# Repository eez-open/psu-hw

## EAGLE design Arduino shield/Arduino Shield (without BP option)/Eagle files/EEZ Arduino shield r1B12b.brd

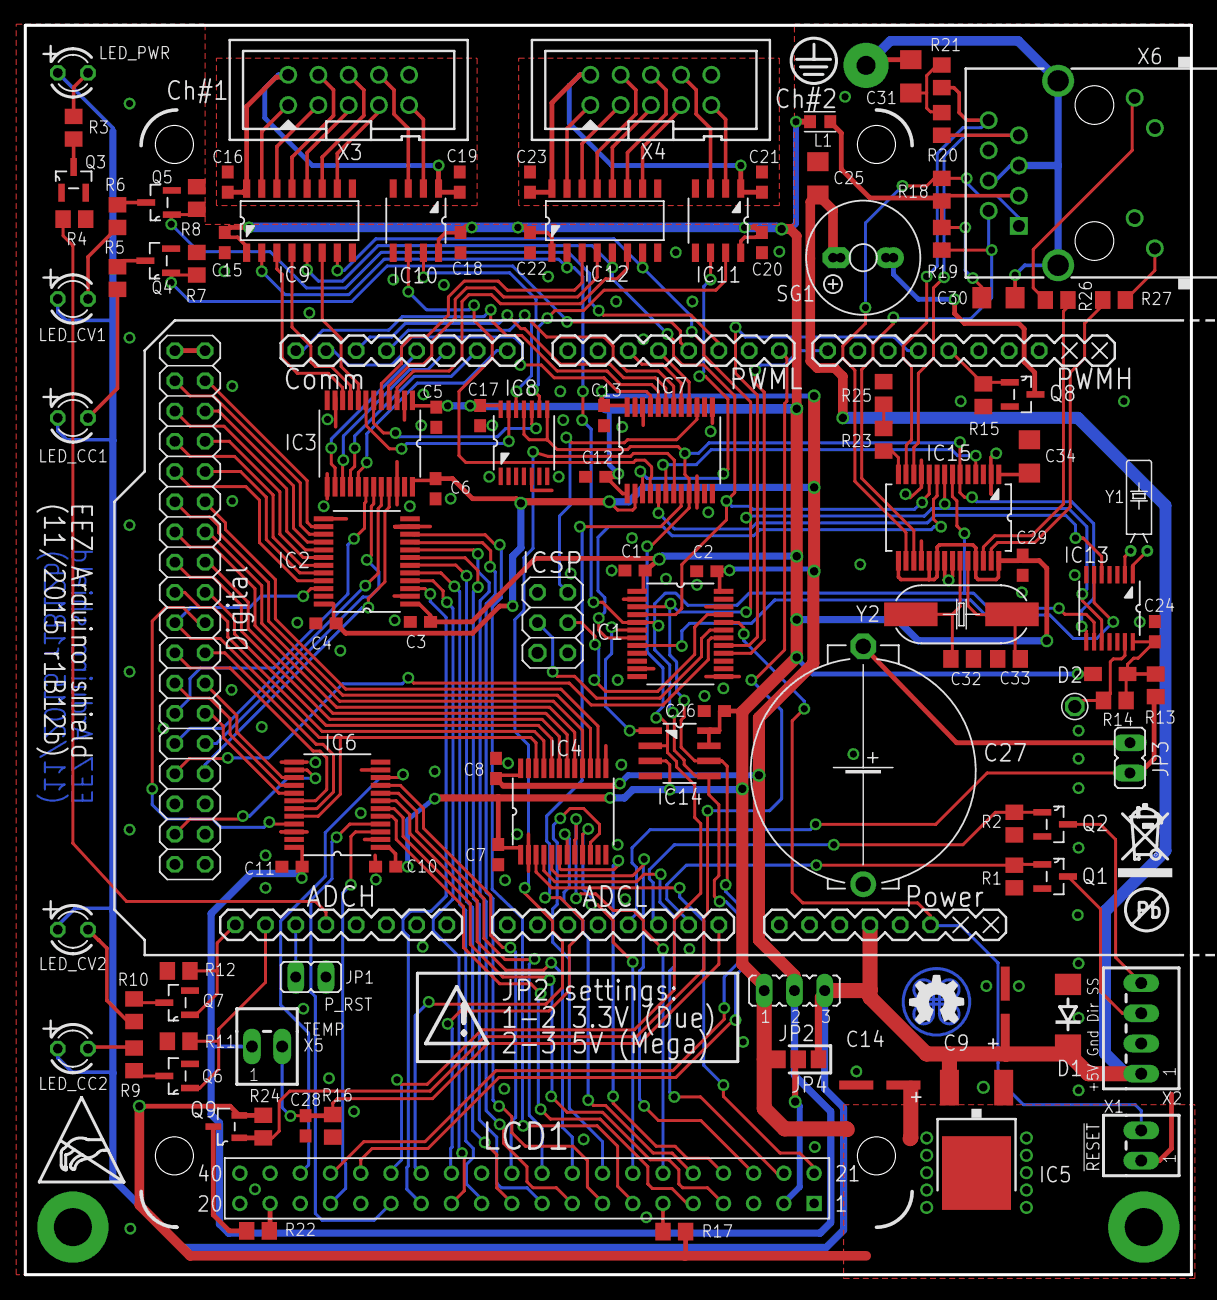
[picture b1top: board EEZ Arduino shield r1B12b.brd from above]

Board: 3 copper layers, 98.0 x 105.0 mm, 114 parts (1 on the bottom side), 167 nets.

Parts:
C1, C2, C3, C4, C5, C6, C7, C8, C10, C11, C12, C13, C15, C16, C17, C18, C19, C20, C21, C22, C23, C24, C26, C28, C29: 100n; C0603
C9: 47u; PANASONIC_C
C14: 10u; PANASONIC_C
C25, C34: 10u; C1206
C27: EECS5R5H105; SG-R20MM
C30, C31: 10n; C1206
C32, C33: 18p; C0805
D1: SMBJ5.0A-TR; DO214AA
D2: BAS316; SOD323-W
EEZ_SIGNATURE: SIGNATURESMALL; SIGNATURE_5MM
IC1, IC2, IC3, IC4, IC6, IC7: SN74LVCC3245ADBRSSOP; SOP65P780X200-24N
IC5: LD1117ADT33TR; DPACK
IC8: SN74LV125APW; SOP65P640X120-14N
IC9, IC12: Si8660EC-B-IS1; SOIC-16
IC10, IC11: SI8620EC-B-IS; SOIC127P600X173-8N
IC13: PCA21125; SOP65P640X120-14N
IC14: AT25256B; SOIC127P600X175-8N
IC15: ENC28J60-I/SS; SOP65P780X200-28N
JP1, JP3: 826926-2; JP1
JP2: 826926-3; JUMPER_3-PIN
JP4: 0R-JUMPA; A0R-JMP
L1: 60R@100MHz; BEAD0603
LCD1: TFT_320QVT; LCD_TFT_320QVT_MIRROR
LED_CC1, LED_CC2: L-934ID; LED3MM
LED_CV1, LED_CV2: L-934YD; LED3MM
LED_PWR: L-934MBC; LED3MM
MCU: ARDUINO+ICSP_MIRROR
Q1, Q2, Q3, Q4, Q5, Q6, Q7, Q8: 2N7002; SOT103P240X110-3N
Q9: IRLML2246TRPBF; SOT95P237X112-3N
R1, R2, R4, R7, R8, R11, R12, R15, R24: 100K; R0805
R3, R5, R6, R9, R10: 240R; R0805
R13: 560R; R0805
R14, R17: 10K; R0805
R16: 4K7; R0805
R18, R19, R20, R21: 50R 0.1%; R0805
R22: 10R; R0805
R23: 2K2 1%; R0805
R25: 120R 1%; R0805
R26, R27: 200R; R0805
SG1: LD-BZEN-0903; BUZZER
SW1: 1301.9316; TACTM-6XN
TP1: PCB_SHIELD_TAB
U$2: RECYCLE_BIN1/8
U$3: PB_SMALL
U$4: ESD_SYMBOL
X1, X5: 22-23-2021
X2: 22-23-2041
X3, X4: 09185106324; IDC-10PIN
X6: LMJTAB881243M-L; RJ45-TRAFO-LED
Y1: 32,768kHz; R26_XTAL
Y2: 25MHz; HC-49/4H

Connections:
3V3LCDSD_CS: IC6.10, LCD1.38
3V3LCD_CS: IC6.4, LCD1.15
3V3LCD_DB0: IC4.3, LCD1.21
3V3LCD_DB1: IC4.4, LCD1.22
3V3LCD_DB2: IC4.5, LCD1.23
3V3LCD_DB3: IC4.6, LCD1.24
3V3LCD_DB4: IC4.7, LCD1.25
3V3LCD_DB5: IC4.8, LCD1.26
3V3LCD_DB6: IC4.9, LCD1.27
3V3LCD_DB7: IC4.10, LCD1.28
3V3LCD_DB8: IC2.10, LCD1.7
3V3LCD_DB9: IC2.9, LCD1.8
3V3LCD_DB10: IC2.8, LCD1.9
3V3LCD_DB11: IC2.7, LCD1.10
3V3LCD_DB12: IC2.6, LCD1.11
3V3LCD_DB13: IC2.5, LCD1.12
3V3LCD_DB14: IC2.4, LCD1.13
3V3LCD_DB15: IC2.3, LCD1.14
3V3LCD_RD: LCD1.6, R17.1
3V3LCD_RESET: IC6.3, LCD1.17
3V3LCD_RS: IC6.6, LCD1.4
3V3LCD_WR: IC6.5, LCD1.5
3V3MISO: IC7.9, IC8.8, IC8.11, IC13.8, IC14.2, IC15.6, LCD1.35
3V3MOSI: IC1.5, IC9.2, IC12.2, IC13.9, IC14.5, IC15.7, LCD1.37
3V3SCLK: IC1.3, IC9.7, IC12.7, IC13.10, IC14.6, IC15.8, LCD1.36
3V3TOUCH_CS: IC6.8, LCD1.30
3V3TOUCH_DIN: IC6.9, LCD1.31
3V3TOUCH_DO: IC7.8, LCD1.33
3V3TOUCH_IRQ: IC7.7, LCD1.34
3V3TOUCH_SCLK: IC6.7, LCD1.29
!3V3ADC1_SELECT: IC3.8, IC9.6
!3V3ADC2_SELECT: IC3.3, IC12.6
!3V3CONVEND1: IC7.4, IC10.6
!3V3CONVEND2: IC7.3, IC11.6
!3V3DAC1_SELECT: IC3.9, IC9.4
!3V3DAC2_SELECT: IC3.4, IC12.4
!3V3EEPROM_SELECT: IC1.6, IC14.1
!3V3ETH_IRQ: IC7.6, IC15.4
!3V3ETH_SELECT: IC1.7, IC15.9
!3V3IO_EXPANDER1: IC3.10, IC9.3
!3V3IO_EXPANDER2: IC3.5, IC12.3
!3V3ISOLATOR1_EN: IC3.7, IC8.13
!3V3ISOLATOR2_EN: IC3.6, IC8.10
!3V3RESET: IC1.4, IC9.5, IC12.5, IC15.10
!3V3RTC_IRQ: IC7.5, IC13.5
!3V3RTC_SELECT: IC1.8, IC13.6
!ADC1_SELECT: IC3.16, MCU.15
!ADC2_SELECT: IC3.21, MCU.48
!CH1_ADC: IC9.11, X3.6
!CH1_DAC: IC9.13, X3.4
!CH1_EXPANDER: IC9.14, X3.3
!CH1_INT: IC10.3, X3.8
!CH1_RESET: IC9.12, X3.5
!CH2_ADC: IC12.11, X4.6
!CH2_DAC: IC12.13, X4.4
!CH2_EXPANDER: IC12.14, X4.3
!CH2_INT: IC11.3, X4.8
!CH2_RESET: IC12.12, X4.5
!CONVEND1: IC7.20, MCU.21
!CONVEND2: IC7.21, MCU.20
!DAC1_SELECT: IC3.15, MCU.16
!DAC2_SELECT: IC3.20, MCU.47
!EEPROM_SELECT: IC1.18, MCU.49
!ETH_IRQ: IC7.18, MCU.18
!ETH_SELECT: IC1.17, MCU.11
!IO_EXPANDER1: IC3.14, MCU.17
!IO_EXPANDER2: IC3.19, MCU.46
!ISOLATOR1_EN: IC3.17, MCU.14
!ISOLATOR2_EN: IC3.18, MCU.45
!PWD_RST: JP1.1, MCU.A13
!RESET: IC1.20, MCU.RESET, SW1.3, SW1.4, X1.2
!RTC_IRQ: IC7.19, MCU.19
!RTC_SELECT: IC1.16, MCU.8
+3V3: C1.1, C3.1, C5.1, C7.1, C10.1, C12.1, C14.1, C15.1, C17.2, C18.1, C20.1, C22.1, C26.1, C29.1, D2.A, IC1.1, IC2.1, IC3.1, IC4.1, IC5.4, IC6.1, IC7.1, IC8.14, IC9.1, IC10.8, IC11.8, IC12.1, IC14.3, IC14.7, IC14.8, IC15.15, IC15.19, IC15.20, IC15.25, IC15.28, JP2.1, JP4.3, L1.P$2, Q9.2, R17.2, R24.2
+5V: C9.1, C25.2, D1.C, IC5.3, JP2.3, JP4.1, LED_CC1.A, LED_CC2.A, LED_CV1.A, LED_CV2.A, LED_PWR.A, MCU.5V, SG1.+, SG1.+B, X2.1
BUZZER: MCU.12, Q8.1, R15.2
CH1_5VDC: C16.1, C19.1, IC9.16, IC10.1, X3.2
CH1_GND: C16.2, C19.2, IC9.9, IC10.4, X3.10
CH1_MISO: IC10.2, X3.9
CH1_MOSI: IC9.15, X3.1
CH1_SCLK: IC9.10, X3.7
CH2_5VDC: C21.1, C23.1, IC11.1, IC12.16, X4.2
CH2_GND: C21.2, C23.2, IC11.4, IC12.9, X4.10
CH2_MISO: IC11.2, X4.9
CH2_MOSI: IC12.15, X4.1
CH2_SCLK: IC12.10, X4.7
EARTH: C30.2, C31.2, X6.4, X6.5, X6.SH1, X6.SH2
ETH_IN+: IC15.13, R21.1, X6.8
ETH_IN-: IC15.12, R20.2, X6.7
ETH_LEDA: IC15.26, R26.1
ETH_LEDB: IC15.27, R27.1
ETH_OUT+: IC15.17, R19.1, X6.2
ETH_OUT-: IC15.16, R18.2, X6.1
GND: C1.2, C2.1, C3.2, C4.1, C5.2, C6.1, C7.2, C8.1, C9.2, C10.2, C11.1, C12.2, C13.1, C14.2, C15.2, C17.1, C18.2, C20.2, C22.2, C24.1, C25.1, C26.2, C27.2, C28.1, C29.2, C32.2, C33.2, C34.1, D1.A, IC1.2, IC1.11, IC1.12, IC1.13, IC1.14, IC1.15, IC1.22, IC2.2, IC2.11, IC2.12, IC2.13, IC3.2, IC3.11, IC3.12, IC3.13, IC3.22, IC4.2, IC4.11, IC4.12, IC4.13, IC5.1, IC6.2, IC6.11, IC6.12, IC6.13, IC6.22, IC7.10, IC7.11, IC7.12, IC7.13, IC7.22, IC8.1, IC8.2, IC8.4, IC8.5, IC8.7, IC9.8, IC10.5, IC11.5, IC12.8, IC13.7, IC14.4, IC15.2, IC15.11, IC15.18, IC15.21, IC15.22, JP1.2, LCD1.1, MCU.GND, MCU.GND1, MCU.GND2, MCU.GND3, MCU.GND4, MCU.ICSP_GND, Q1.2, Q2.2, Q3.2, Q4.2, Q5.2, Q6.2, Q7.2, Q8.2, R1.2, R2.2, R4.2, R7.2, R8.2, R11.2, R12.2, R15.1, R16.2, R25.2, SW1.1, SW1.2, SW1.5, X1.1, X2.2, X6.10, X6.11
LCDSD_CS: IC6.14, MCU.53
LCD_BRIGHTNESS: MCU.7, Q9.1, R24.1
LCD_CS: IC2.22, IC4.22, IC6.20, MCU.39
LCD_DB0: IC4.21, MCU.37
LCD_DB1: IC4.20, MCU.36
LCD_DB2: IC4.19, MCU.35
LCD_DB3: IC4.18, MCU.34
LCD_DB4: IC4.17, MCU.33
LCD_DB5: IC4.16, MCU.32
LCD_DB6: IC4.15, MCU.31
LCD_DB7: IC4.14, MCU.30
LCD_DB8: IC2.14, MCU.22
LCD_DB9: IC2.15, MCU.23
LCD_DB10: IC2.16, MCU.24
LCD_DB11: IC2.17, MCU.25
LCD_DB12: IC2.18, MCU.26
LCD_DB13: IC2.19, MCU.27
LCD_DB14: IC2.20, MCU.28
LCD_DB15: IC2.21, MCU.29
LCD_RESET: IC6.21, MCU.38
LCD_RS: IC6.18, MCU.41
LCD_WR: IC6.19, MCU.40
LED_A: LCD1.19, R22.2
LED_CC1: MCU.4, Q4.1, R7.1
LED_CC2: MCU.A14, Q6.1, R11.1
LED_CV1: MCU.5, Q5.1, R8.1
LED_CV2: MCU.A15, Q7.1, R12.1
LED_PWR: MCU.A12, R4.1
MISO: IC7.15, MCU.ICSP_MISO
MOSI: IC1.19, MCU.ICSP_MOSI
unnamed: Q3.3, R3.2
unnamed: LED_PWR.K, R3.1
unnamed: JP4.2, LCD1.2
unnamed: LED_CV1.K, R6.2
unnamed: Q6.3, R9.2
unnamed: Q9.3, R22.1
unnamed: LED_CV2.K, R10.2
unnamed: LED_CC2.K, R9.1
unnamed: MCU.5V(1), MCU.5V(2)
unnamed: Q4.3, R5.2
unnamed: Q7.3, R10.1
unnamed: IC13.1, Y1.2
unnamed: IC13.2, Y1.1
unnamed: Q5.3, R6.1
unnamed: LED_CC1.K, R5.1
unnamed: R23.2, R25.1
unnamed: Q8.3, SG1.-, SG1.-B
unnamed: IC13.13, R14.2, TP1.1
unnamed: C27.1, JP3.2
unnamed: C32.1, IC15.23, Y2.2
unnamed: C33.1, IC15.24, Y2.1
unnamed: C34.2, IC15.1
unnamed: IC15.14, R23.1
unnamed: C24.2, D2.C, IC13.14, R13.2, R14.1
unnamed: R26.2, X6.12
unnamed: R27.2, X6.9
unnamed: C31.1, R20.1, R21.2
unnamed: C30.1, L1.P$1, R18.1, R19.2, X6.3
unnamed: IC8.12, IC10.7
unnamed: IC8.9, IC11.7
PWRDIR: MCU.A1, Q1.1, R1.1
PWRSS: MCU.A2, Q2.1, R2.1
PWR_DIRECT: Q1.3, X2.3
PWR_SSTART: Q2.3, X2.4
RTC_BATT: JP3.1, MCU.A3, R13.1
SCLK: IC1.21, MCU.ICSP_SCK
TEMP_ANALOG: C28.2, MCU.A0, R16.1, X5.2
TOUCH_CS: IC6.16, MCU.43
TOUCH_DIN: IC6.15, MCU.42
TOUCH_DOUT: IC7.16, MCU.3
TOUCH_IRQ: IC7.17, MCU.2
TOUCH_SCLK: IC6.17, MCU.44
VCC: C2.2, C4.2, C6.2, C8.2, C11.2, C13.2, IC1.24, IC2.24, IC3.24, IC4.24, IC6.24, IC7.2, IC7.24, JP2.2, X5.1

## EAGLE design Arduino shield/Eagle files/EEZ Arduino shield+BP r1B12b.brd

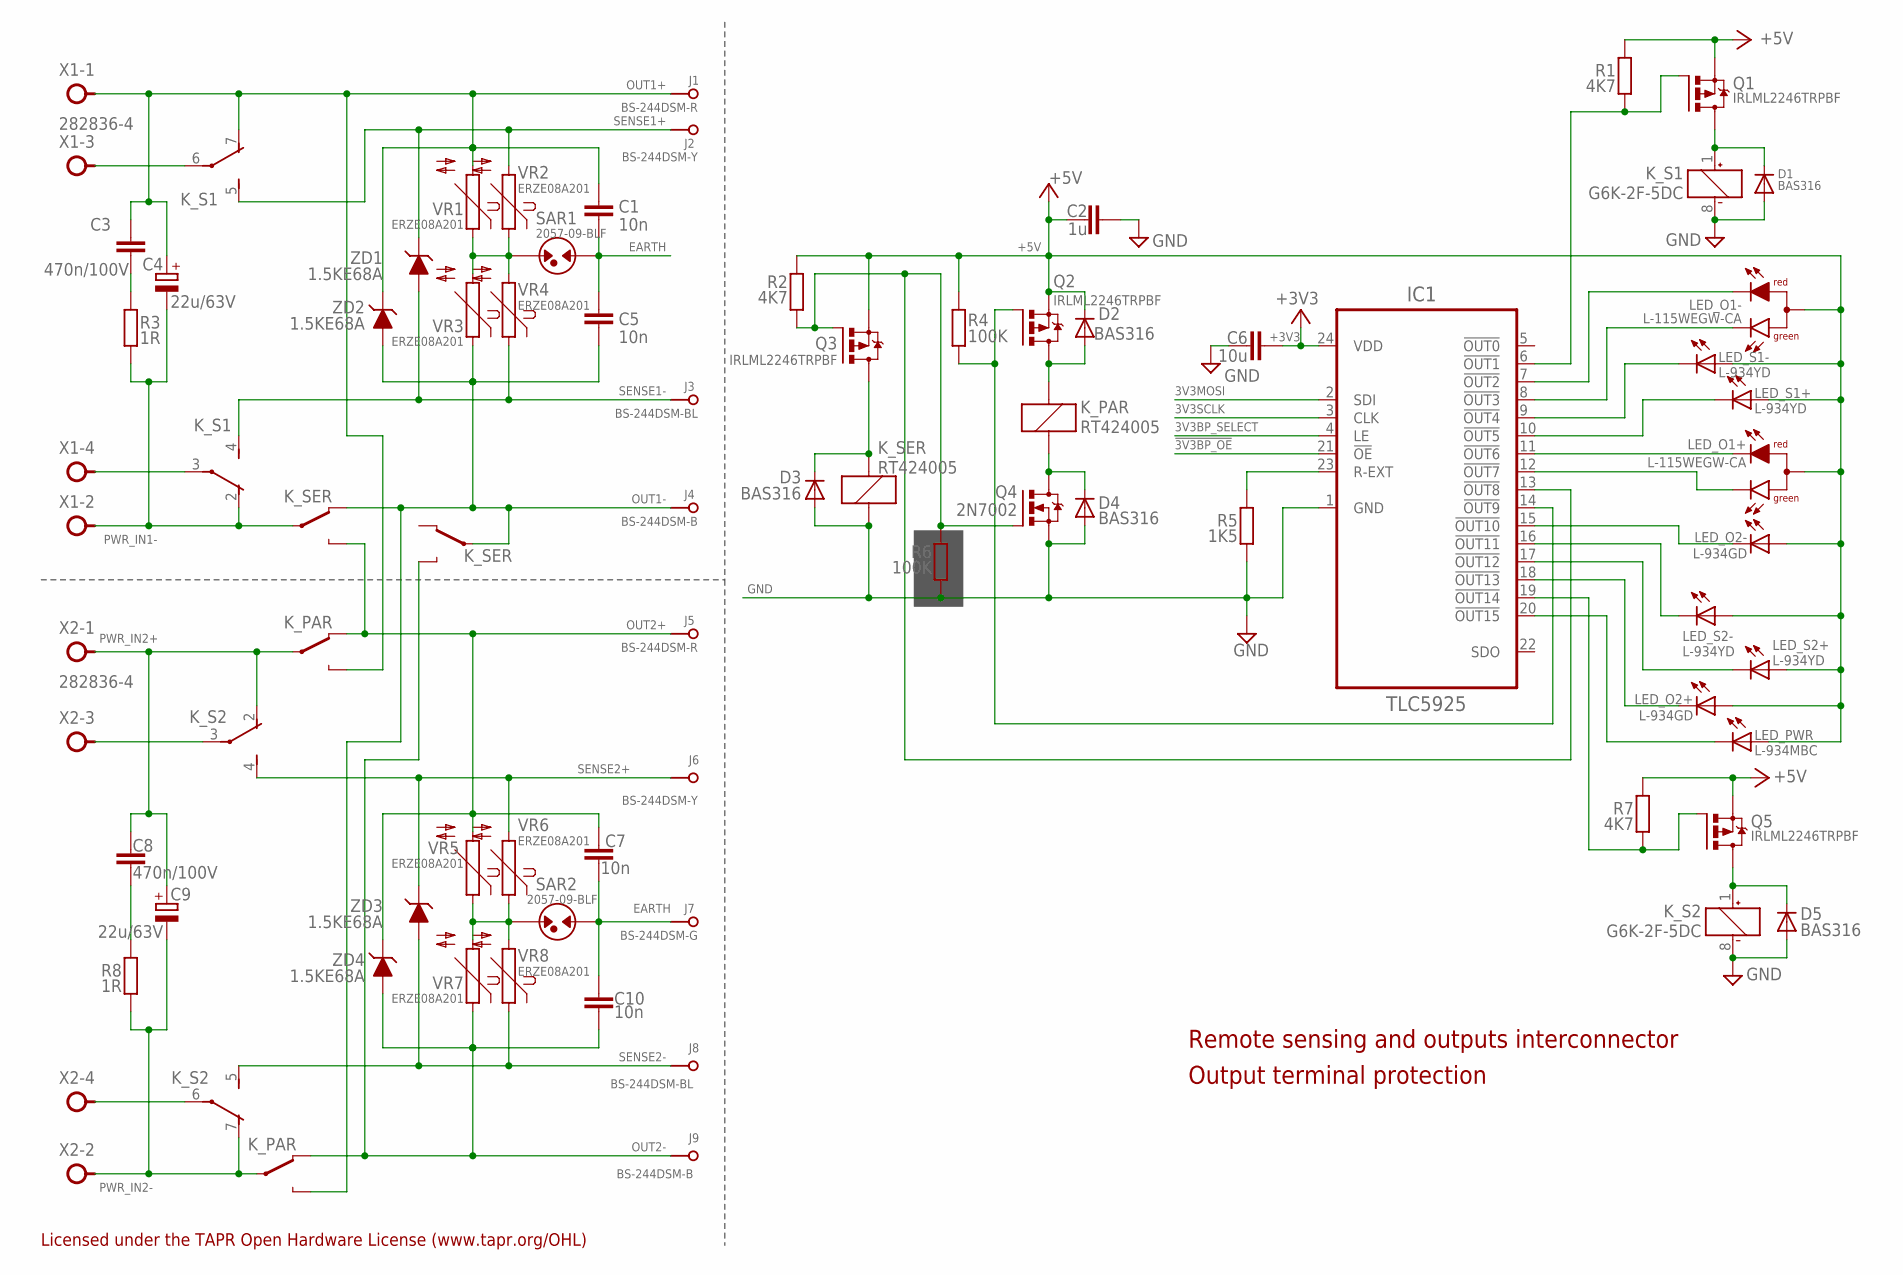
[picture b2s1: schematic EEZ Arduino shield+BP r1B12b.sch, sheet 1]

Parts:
C1, C5, C7, C10: 10n; C1206
C2: 1u; C0805
C3, C8: 470n/100V; C1812
C4, C9: 22u/63V; CAPAE660X610N_COMBO2
C6: 10u; C1206
D1, D2, D3, D4, D5: BAS316; SOD323-W
IC1: TLC5925; SOP63P600X175-24N
J1, J5: BS-244DSM-R; BP_5_12/15WHITE
J2, J6: BS-244DSM-Y; BP_5_12/15BLK
J3, J8: BS-244DSM-BL; BP_5_12/15BLK
J4, J9: BS-244DSM-B; BP_5_12/15WHITE
J7: BS-244DSM-G; BP_5_12/15BLK
K_PAR: RT424005; RT-C/016A5
K_S1, K_S2: G6K-2F-5DC; G6K-2F; MPN G6K-2F DC24
K_SER: RT424005; RT-C/016A5
LED_O1+, LED_O1-: L-115WEGW-CA; DUO_LED3MM
LED_O2+, LED_O2-: L-934GD; LED3MM
LED_PWR: L-934MBC; LED3MM
LED_S1+, LED_S1-, LED_S2+, LED_S2-: L-934YD; LED3MM
Q1, Q2, Q3, Q5: IRLML2246TRPBF; SOT95P237X112-3N
Q4: 2N7002; SOT103P240X110-3N
R1, R2, R7: 4K7; R0805
R3, R8: 1R; R0805
R4, R6: 100K; R0805
R5: 1K5; R0805
SAR1, SAR2: 2057-09-BLF; SAR
VR1, VR2, VR3, VR4, VR5, VR6, VR7, VR8: ERZE08A201; S10K175
X1, X2: 282836-4; TBLOCK5.0_4S
ZD1, ZD2, ZD3, ZD4: 1.5KE68A; DO201

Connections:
3V3BP_SELECT: IC1.4 (LE); also elsewhere on the board
3V3MOSI: IC1.2 (SDI); also elsewhere on the board
3V3SCLK: IC1.3 (CLK); also elsewhere on the board
!3V3BP_OE: IC1.21 (!OE); also elsewhere on the board
!BP_OUT1: IC1.6 (!OUT1), Q1.1 (G), R1.1
!BP_OUT2: IC1.7 (!OUT2), LED_O1-.A (CR)
!BP_OUT3: IC1.8 (!OUT3), LED_O1-.AG (CG)
!BP_OUT4: IC1.9 (!OUT4), LED_S1-.K (C)
!BP_OUT5: IC1.10 (!OUT5), LED_S1+.K (C)
!BP_OUT6: IC1.11 (!OUT6), LED_O1+.A (CR)
!BP_OUT7: IC1.12 (!OUT7), LED_O1+.AG (CG)
!BP_OUT8: IC1.13 (!OUT8), Q3.1 (G), Q4.1 (G), R2.1, R6.2
!BP_OUT9: IC1.14 (!OUT9), Q2.1 (G), R4.1
!BP_OUT10: IC1.15 (!OUT10), LED_O2-.K (C)
!BP_OUT11: IC1.16 (!OUT11), LED_S2-.K (C)
!BP_OUT12: IC1.17 (!OUT12), LED_S2+.K (C)
!BP_OUT13: IC1.18 (!OUT13), LED_O2+.K (C)
!BP_OUT14: IC1.19 (!OUT14), Q5.1 (G), R7.1
!BP_OUT15: IC1.20 (!OUT15), LED_PWR.K (C)
+3V3: C6.1, IC1.24 (VDD); also elsewhere on the board
+5V: C2.1, D2.C, LED_O1+.C (A), LED_O1-.C (A), LED_O2+.A, LED_O2-.A, LED_PWR.A, LED_S1+.A, LED_S1-.A, LED_S2+.A, LED_S2-.A, Q1.2 (S), Q2.2 (S), Q3.2 (S), Q5.2 (S), R1.2, R2.2, R4.2, R7.2; also elsewhere on the board
EARTH: C1.2, C5.1, C7.2, C10.1, J7.P$1, SAR1.P$1, SAR2.P$1; also elsewhere on the board
GND: C2.2, C6.2, D1.A, D3.A, D4.A, D5.A, IC1.1 (GND), K_S1.8 (-), K_S2.8 (-), K_SER.A1 (C2), Q4.2 (S), R5.1, R6.1; also elsewhere on the board
unnamed: K_S2.6, X2.P$4
unnamed: K_S1.6, X1.P$3
unnamed: K_S2.3, X2.P$3
unnamed: D1.C, K_S1.1 (+), Q1.3 (D)
unnamed: D5.C, K_S2.1 (+), Q5.3 (D)
unnamed: C3.2, R3.2
unnamed: C8.2, R8.2
unnamed: K_S1.3, X1.P$4
unnamed: D3.C, K_SER.A2 (C1), Q3.3 (D)
unnamed: D2.A, K_PAR.A1 (C2), Q2.3 (D)
unnamed: IC1.23 (R-EXT), R5.2
unnamed: SAR1.P$2, VR1.1, VR2.1, VR3.2, VR4.2
unnamed: SAR2.P$2, VR5.1, VR6.1, VR7.2, VR8.2
OUT1+: C1.1, C3.1, C4.1 (+), C4.1.1 (+), J1.P$1, K_PAR.14A (O), K_S1.7 (O), VR1.2, X1.P$1, ZD2.C (1)
OUT1-: C5.2, J4.P$1, K_PAR.14B (O), K_SER.11B, K_SER.12A (S), VR3.1, ZD2.A (2)
OUT2+: C7.1, J5.P$1, K_PAR.12A (S), K_SER.14A (O), VR5.2, ZD4.C (1)
OUT2-: C10.2, J9.P$1, K_PAR.12B (S), K_SER.14B (O), VR7.1, ZD4.A (2)
PWR_IN1-: C4.2 (-), C4.2.1 (-), K_S1.2 (O), K_SER.11A, R3.1, X1.P$2
PWR_IN2+: C8.1, C9.1 (+), C9.1.1 (+), K_PAR.11A, K_S2.2 (O), X2.P$1
PWR_IN2-: C9.2 (-), C9.2.1 (-), K_PAR.11B, K_S2.7 (O), R8.1, X2.P$2
SENSE1+: J2.P$1, K_S1.5 (S), VR2.2, ZD1.C (1)
SENSE1-: J3.P$1, K_S1.4 (S), VR4.1, ZD1.A (2)
SENSE2+: J6.P$1, K_S2.4 (S), VR6.2, ZD3.C (1)
SENSE2-: J8.P$1, K_S2.5 (S), VR8.1, ZD3.A (2)
V-2: D4.C, K_PAR.A2 (C1), Q4.3 (D)

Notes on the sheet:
Remote sensing and outputs interconnector
Output terminal protection
Licensed under the TAPR Open Hardware License (www.tapr.org/OHL)

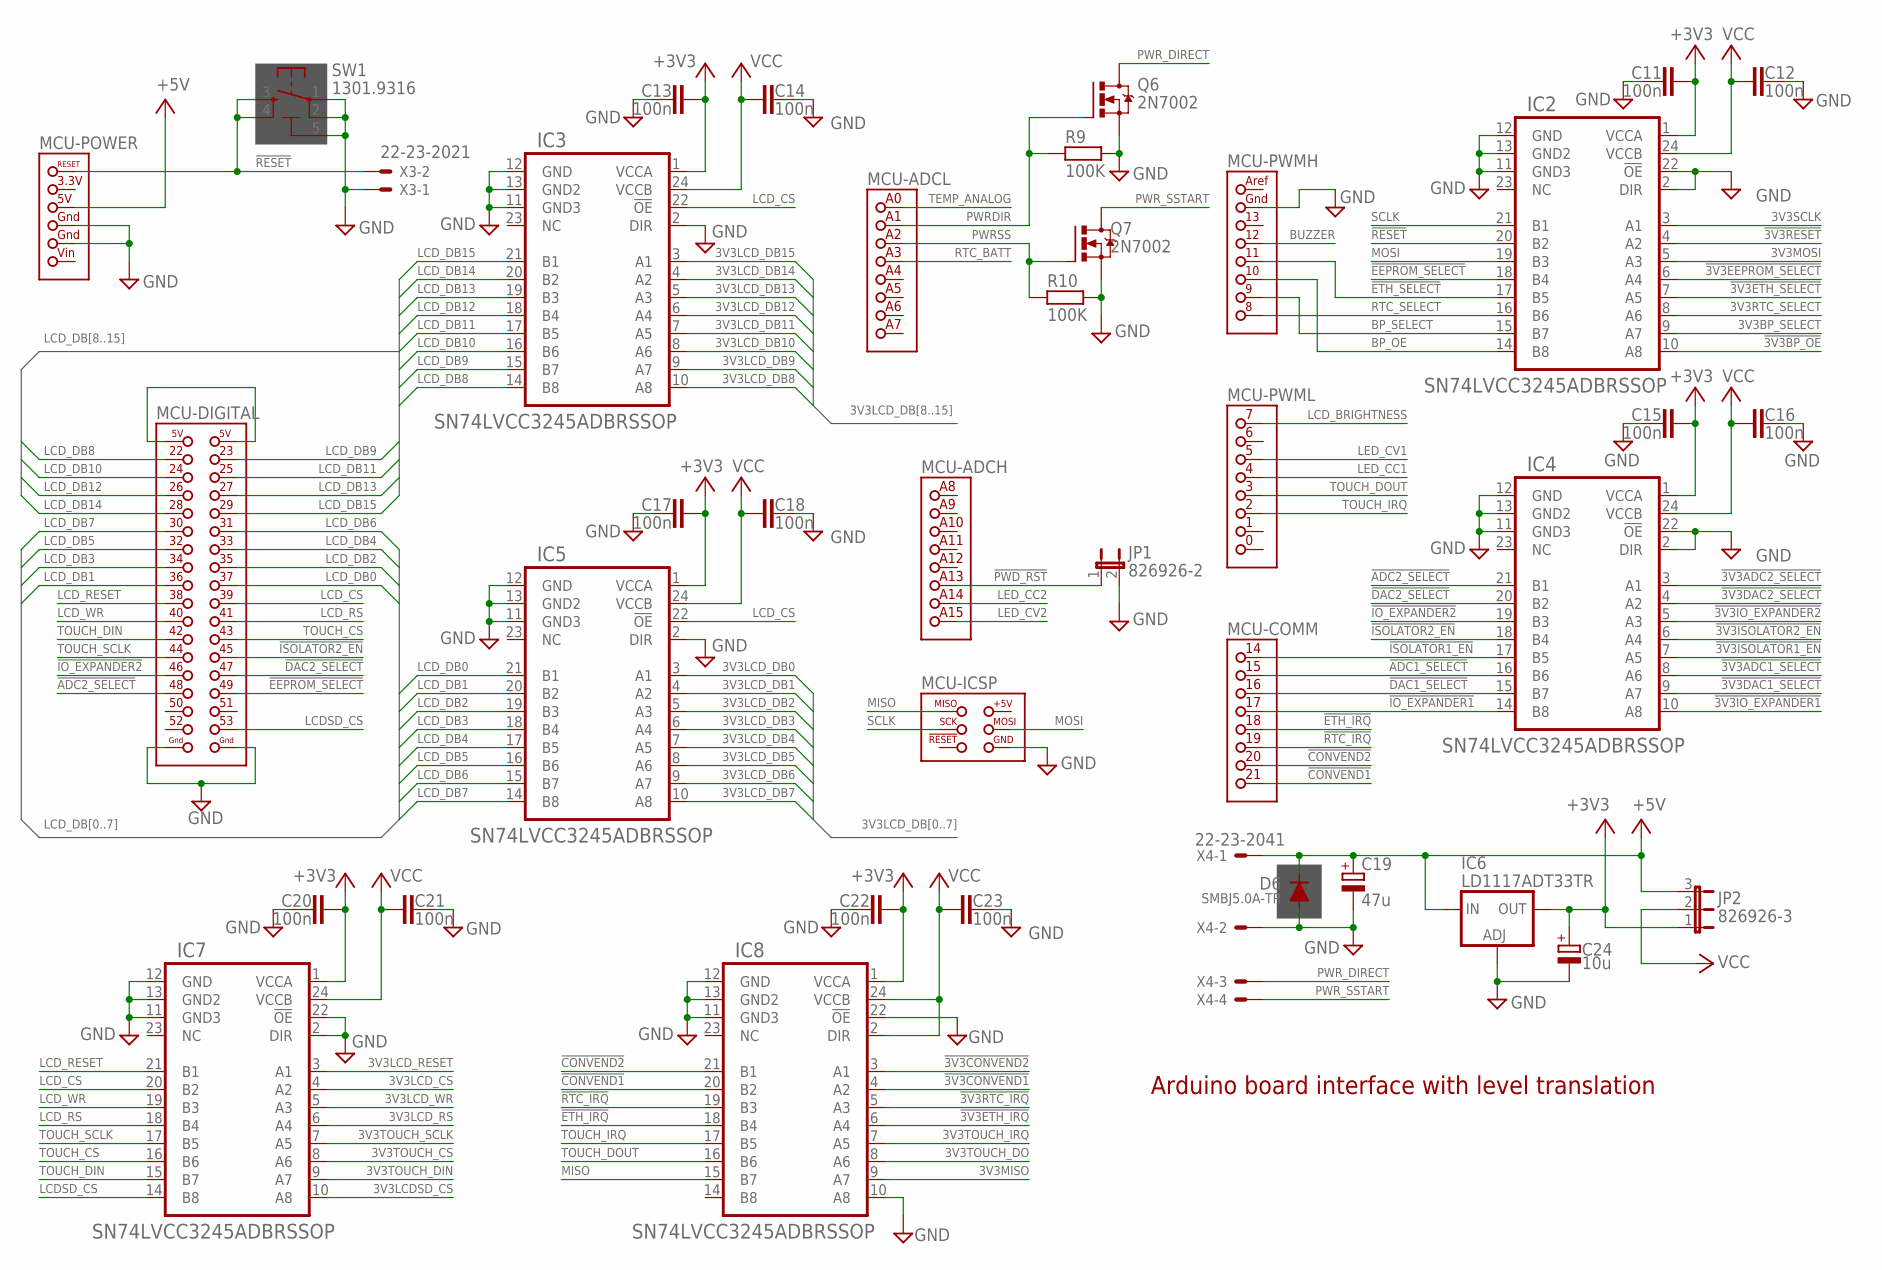
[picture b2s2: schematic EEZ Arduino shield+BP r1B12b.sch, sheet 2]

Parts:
C11, C12, C13, C14, C15, C16, C17, C18, C20, C21, C22, C23: 100n; C0603
C19: 47u; PANASONIC_C
C24: 10u; PANASONIC_C
D6: SMBJ5.0A-TR; DO214AA
IC2, IC3, IC4, IC5, IC7, IC8: SN74LVCC3245ADBRSSOP; SOP65P780X200-24N
IC6: LD1117ADT33TR; DPACK
JP1: 826926-2; JP1
JP2: 826926-3; JUMPER_3-PIN
MCU: ARDUINO_MEGA+ICSPMIRROR; ARDUINO+ICSP_MIRROR
Q6, Q7: 2N7002; SOT103P240X110-3N
R9, R10: 100K; R0805
SW1: 1301.9316; TACTM-6XN
X3: 22-23-2021; MPN 22-23-2021
X4: 22-23-2041; MPN 22-23-2041

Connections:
3V3BP_SELECT: IC2.9 (A7); also elsewhere on the board
3V3LCDSD_CS: IC7.10 (A8); also elsewhere on the board
3V3LCD_CS: IC7.4 (A2); also elsewhere on the board
3V3LCD_DB0: IC5.3 (A1); also elsewhere on the board
3V3LCD_DB1: IC5.4 (A2); also elsewhere on the board
3V3LCD_DB2: IC5.5 (A3); also elsewhere on the board
3V3LCD_DB3: IC5.6 (A4); also elsewhere on the board
3V3LCD_DB4: IC5.7 (A5); also elsewhere on the board
3V3LCD_DB5: IC5.8 (A6); also elsewhere on the board
3V3LCD_DB6: IC5.9 (A7); also elsewhere on the board
3V3LCD_DB7: IC5.10 (A8); also elsewhere on the board
3V3LCD_DB8: IC3.10 (A8); also elsewhere on the board
3V3LCD_DB9: IC3.9 (A7); also elsewhere on the board
3V3LCD_DB10: IC3.8 (A6); also elsewhere on the board
3V3LCD_DB11: IC3.7 (A5); also elsewhere on the board
3V3LCD_DB12: IC3.6 (A4); also elsewhere on the board
3V3LCD_DB13: IC3.5 (A3); also elsewhere on the board
3V3LCD_DB14: IC3.4 (A2); also elsewhere on the board
3V3LCD_DB15: IC3.3 (A1); also elsewhere on the board
3V3LCD_RESET: IC7.3 (A1); also elsewhere on the board
3V3LCD_RS: IC7.6 (A4); also elsewhere on the board
3V3LCD_WR: IC7.5 (A3); also elsewhere on the board
3V3MISO: IC8.9 (A7); also elsewhere on the board
3V3MOSI: IC2.5 (A3); also elsewhere on the board
3V3RTC_SELECT: IC2.8 (A6); also elsewhere on the board
3V3SCLK: IC2.3 (A1); also elsewhere on the board
3V3TOUCH_CS: IC7.8 (A6); also elsewhere on the board
3V3TOUCH_DIN: IC7.9 (A7); also elsewhere on the board
3V3TOUCH_DO: IC8.8 (A6); also elsewhere on the board
3V3TOUCH_IRQ: IC8.7 (A5); also elsewhere on the board
3V3TOUCH_SCLK: IC7.7 (A5); also elsewhere on the board
!3V3ADC1_SELECT: IC4.8 (A6); also elsewhere on the board
!3V3ADC2_SELECT: IC4.3 (A1); also elsewhere on the board
!3V3BP_OE: IC2.10 (A8); also elsewhere on the board
!3V3CONVEND1: IC8.4 (A2); also elsewhere on the board
!3V3CONVEND2: IC8.3 (A1); also elsewhere on the board
!3V3DAC1_SELECT: IC4.9 (A7); also elsewhere on the board
!3V3DAC2_SELECT: IC4.4 (A2); also elsewhere on the board
!3V3EEPROM_SELECT: IC2.6 (A4); also elsewhere on the board
!3V3ETH_IRQ: IC8.6 (A4); also elsewhere on the board
!3V3ETH_SELECT: IC2.7 (A5); also elsewhere on the board
!3V3IO_EXPANDER1: IC4.10 (A8); also elsewhere on the board
!3V3IO_EXPANDER2: IC4.5 (A3); also elsewhere on the board
!3V3ISOLATOR1_EN: IC4.7 (A5); also elsewhere on the board
!3V3ISOLATOR2_EN: IC4.6 (A4); also elsewhere on the board
!3V3RESET: IC2.4 (A2); also elsewhere on the board
!3V3RTC_IRQ: IC8.5 (A3); also elsewhere on the board
!ADC1_SELECT: IC4.16 (B6), MCU.15
!ADC2_SELECT: IC4.21 (B1), MCU.48 (48(PL3))
!CONVEND1: IC8.20 (B2), MCU.21
!CONVEND2: IC8.21 (B1), MCU.20
!DAC1_SELECT: IC4.15 (B7), MCU.16
!DAC2_SELECT: IC4.20 (B2), MCU.47 (47(PL4))
!EEPROM_SELECT: IC2.18 (B4), MCU.49 (49(PL2))
!ETH_IRQ: IC8.18 (B4), MCU.18
!ETH_SELECT: IC2.17 (B5), MCU.11
!IO_EXPANDER1: IC4.14 (B8), MCU.17
!IO_EXPANDER2: IC4.19 (B3), MCU.46 (46(PL5))
!ISOLATOR1_EN: IC4.17 (B5), MCU.14
!ISOLATOR2_EN: IC4.18 (B4), MCU.45 (45(PL6))
!PWD_RST: JP1.1, MCU.A13 (ADC13)
!RESET: IC2.20 (B2), MCU.RESET (!RESET), SW1.3, SW1.4, X3.2
!RTC_IRQ: IC8.19 (B3), MCU.19
+3V3: C11.1, C13.1, C15.1, C17.1, C20.1, C22.1, C24.1 (+), IC2.1 (VCCA), IC3.1 (VCCA), IC4.1 (VCCA), IC5.1 (VCCA), IC6.4 (OUT), IC7.1 (VCCA), IC8.1 (VCCA), JP2.1; also elsewhere on the board
+5V: C19.1 (+), D6.C, IC6.3 (IN), JP2.3, MCU.5V, X4.1; also elsewhere on the board
BP_OE: IC2.14 (B8), MCU.10
BP_SELECT: IC2.15 (B7), MCU.9 (9(PH6))
BUZZER: MCU.12; also elsewhere on the board
GND: C11.2, C12.1, C13.2, C14.1, C15.2, C16.1, C17.2, C18.1, C19.2 (-), C20.2, C21.1, C22.2, C23.1, C24.2 (-), D6.A, IC2.2 (DIR), IC2.11 (GND3), IC2.12 (GND), IC2.13 (GND2), IC2.22 (!OE), IC3.2 (DIR), IC3.11 (GND3), IC3.12 (GND), IC3.13 (GND2), IC4.2 (DIR), IC4.11 (GND3), IC4.12 (GND), IC4.13 (GND2), IC4.22 (!OE), IC5.2 (DIR), IC5.11 (GND3), IC5.12 (GND), IC5.13 (GND2), IC6.1 (ADJ), IC7.2 (DIR), IC7.11 (GND3), IC7.12 (GND), IC7.13 (GND2), IC7.22 (!OE), IC8.10 (A8), IC8.11 (GND3), IC8.12 (GND), IC8.13 (GND2), IC8.22 (!OE), JP1.2, MCU.GND, MCU.GND1, MCU.GND2, MCU.GND3, MCU.GND4, MCU.ICSP_GND (GND), Q6.2 (S), Q7.2 (S), R9.2, R10.2, SW1.1, SW1.2, SW1.5 (5-GND), X3.1, X4.2; also elsewhere on the board
LCDSD_CS: IC7.14 (B8), MCU.53 (53(PB2/MOSI))
LCD_BRIGHTNESS: MCU.7 (7(PH4)); also elsewhere on the board
LCD_CS: IC3.22 (!OE), IC5.22 (!OE), IC7.20 (B2), MCU.39 (39(PC0))
LCD_DB0: IC5.21 (B1), MCU.37 (37(PC2))
LCD_DB1: IC5.20 (B2), MCU.36 (36(PC3))
LCD_DB2: IC5.19 (B3), MCU.35 (35(PC4))
LCD_DB3: IC5.18 (B4), MCU.34 (34(PC5))
LCD_DB4: IC5.17 (B5), MCU.33 (33(PC6))
LCD_DB5: IC5.16 (B6), MCU.32 (32(PC7))
LCD_DB6: IC5.15 (B7), MCU.31 (31(PA7))
LCD_DB7: IC5.14 (B8), MCU.30 (30(PA6))
LCD_DB8: IC3.14 (B8), MCU.22
LCD_DB9: IC3.15 (B7), MCU.23
LCD_DB10: IC3.16 (B6), MCU.24 (24(PA0))
LCD_DB11: IC3.17 (B5), MCU.25 (25(PA1))
LCD_DB12: IC3.18 (B4), MCU.26 (26(PA2))
LCD_DB13: IC3.19 (B3), MCU.27 (27(PA3))
LCD_DB14: IC3.20 (B2), MCU.28 (28(PA4))
LCD_DB15: IC3.21 (B1), MCU.29 (29(PA5))
LCD_RESET: IC7.21 (B1), MCU.38 (38(PC1))
LCD_RS: IC7.18 (B4), MCU.41 (41(PG2))
LCD_WR: IC7.19 (B3), MCU.40 (40(PD7))
LED_CC1: MCU.4 (4(PG5)); also elsewhere on the board
LED_CC2: MCU.A14 (ADC14); also elsewhere on the board
LED_CV1: MCU.5 (5(PE3)); also elsewhere on the board
LED_CV2: MCU.A15 (ADC15); also elsewhere on the board
MISO: IC8.15 (B7), MCU.ICSP_MISO (MISO)
MOSI: IC2.19 (B3), MCU.ICSP_MOSI (MOSI)
unnamed: MCU.5V(1), MCU.5V(2)
PWRDIR: MCU.A1 (ADC1), Q6.1 (G), R9.1
PWRSS: MCU.A2 (ADC2), Q7.1 (G), R10.1
PWR_DIRECT: Q6.3 (D), X4.3
PWR_SSTART: Q7.3 (D), X4.4
RTC_BATT: MCU.A3 (ADC3); also elsewhere on the board
RTC_SELECT: IC2.16 (B6), MCU.8 (8(PH5))
SCLK: IC2.21 (B1), MCU.ICSP_SCK (SCK)
TEMP_ANALOG: MCU.A0 (ADC0); also elsewhere on the board
TOUCH_CS: IC7.16 (B6), MCU.43 (43(PG0))
TOUCH_DIN: IC7.15 (B7), MCU.42 (42(PG1))
TOUCH_DOUT: IC8.16 (B6), MCU.3 (3(PE5))
TOUCH_IRQ: IC8.17 (B5), MCU.2 (2(PE4))
TOUCH_SCLK: IC7.17 (B5), MCU.44 (44(PL7))
VCC: C12.2, C14.2, C16.2, C18.2, C21.2, C23.2, IC2.24 (VCCB), IC3.24 (VCCB), IC4.24 (VCCB), IC5.24 (VCCB), IC7.24 (VCCB), IC8.2 (DIR), IC8.24 (VCCB), JP2.2; also elsewhere on the board

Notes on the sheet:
Arduino board interface with level translation

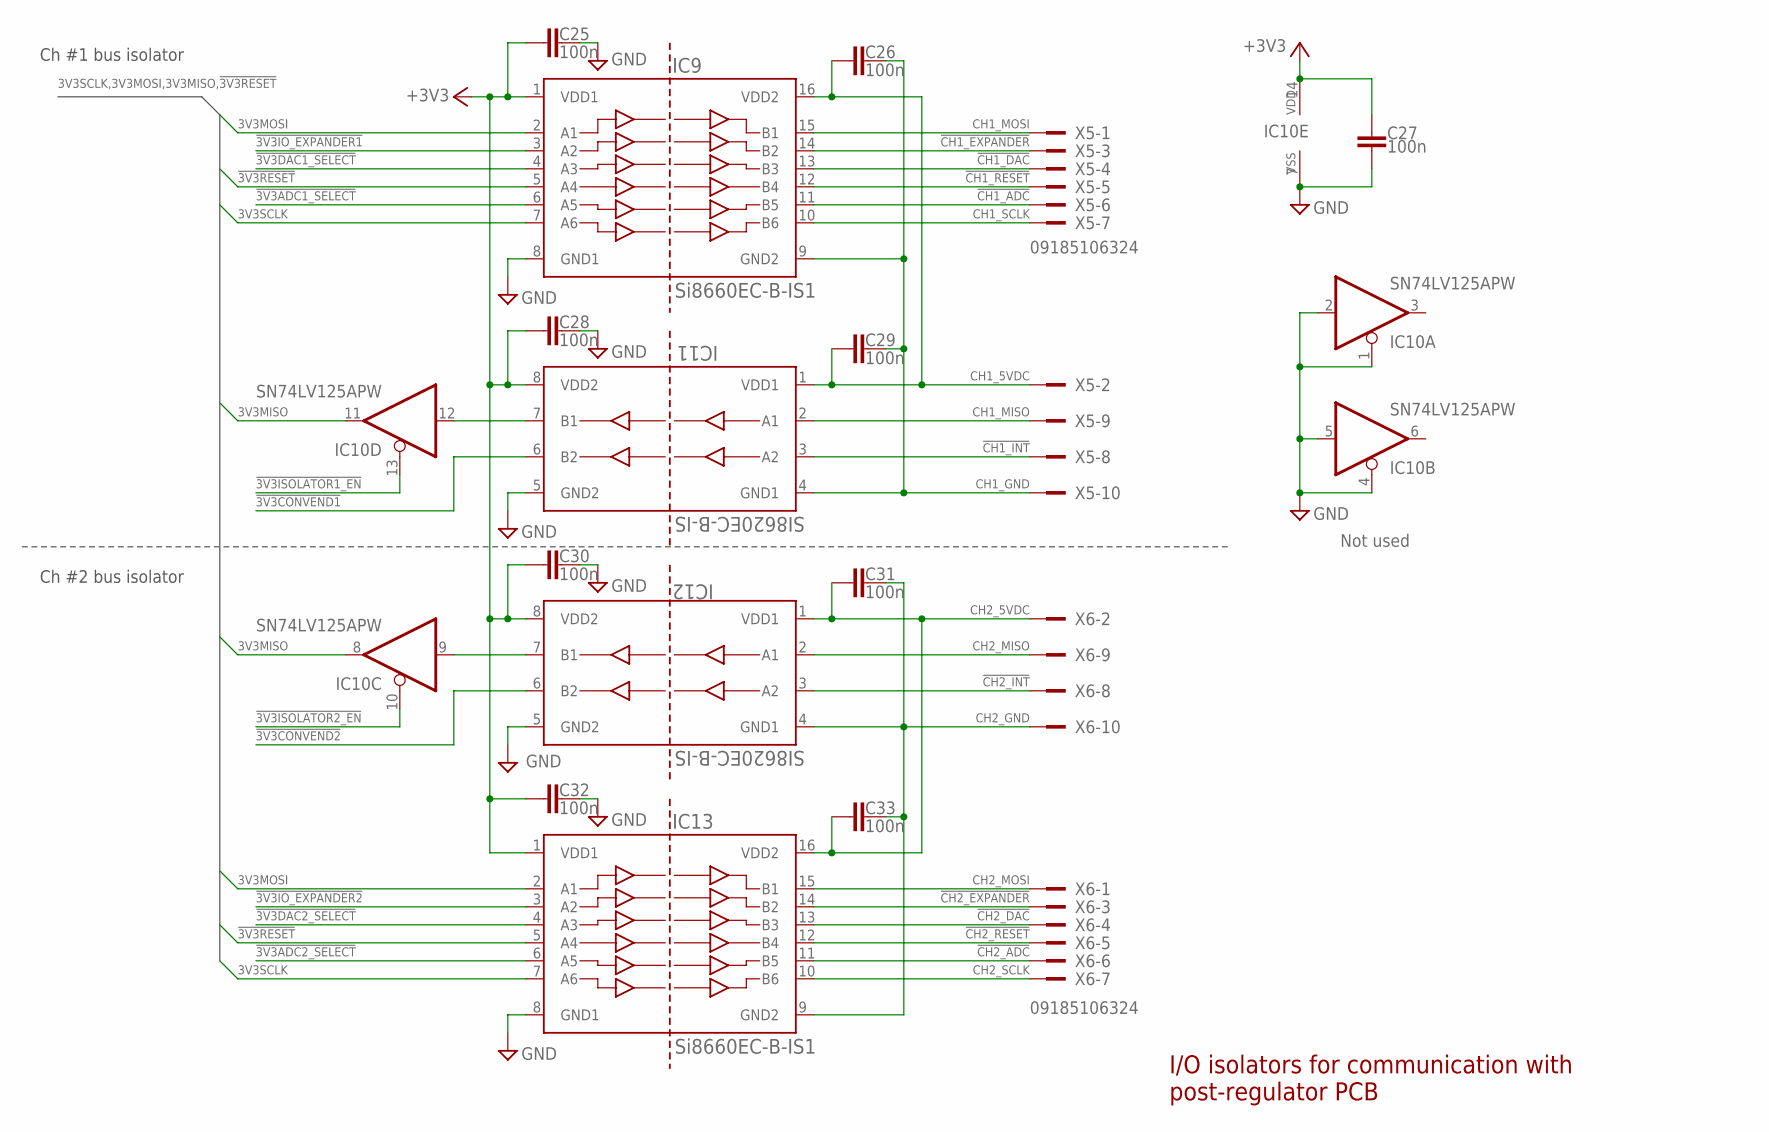
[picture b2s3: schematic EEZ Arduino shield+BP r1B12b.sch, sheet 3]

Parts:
C25, C26, C27, C28, C29, C30, C31, C32, C33: 100n; C0603
IC9, IC13: Si8660EC-B-IS1; SOIC-16
IC10: SN74LV125APW; SOP65P640X120-14N
IC11, IC12: SI8620EC-B-IS; SOIC127P600X173-8N
X5, X6: 09185106324; IDC-10PIN

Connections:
3V3MISO: IC10.8 (O), IC10.11 (O); also elsewhere on the board
3V3MOSI: IC9.2 (A1), IC13.2 (A1); also elsewhere on the board
3V3SCLK: IC9.7 (A6), IC13.7 (A6); also elsewhere on the board
!3V3ADC1_SELECT: IC9.6 (A5); also elsewhere on the board
!3V3ADC2_SELECT: IC13.6 (A5); also elsewhere on the board
!3V3CONVEND1: IC11.6 (B2); also elsewhere on the board
!3V3CONVEND2: IC12.6 (B2); also elsewhere on the board
!3V3DAC1_SELECT: IC9.4 (A3); also elsewhere on the board
!3V3DAC2_SELECT: IC13.4 (A3); also elsewhere on the board
!3V3IO_EXPANDER1: IC9.3 (A2); also elsewhere on the board
!3V3IO_EXPANDER2: IC13.3 (A2); also elsewhere on the board
!3V3ISOLATOR1_EN: IC10.13 (OE); also elsewhere on the board
!3V3ISOLATOR2_EN: IC10.10 (OE); also elsewhere on the board
!3V3RESET: IC9.5 (A4), IC13.5 (A4); also elsewhere on the board
!CH1_ADC: IC9.11 (B5), X5.6
!CH1_DAC: IC9.13 (B3), X5.4
!CH1_EXPANDER: IC9.14 (B2), X5.3
!CH1_INT: IC11.3 (A2), X5.8
!CH1_RESET: IC9.12 (B4), X5.5
!CH2_ADC: IC13.11 (B5), X6.6
!CH2_DAC: IC13.13 (B3), X6.4
!CH2_EXPANDER: IC13.14 (B2), X6.3
!CH2_INT: IC12.3 (A2), X6.8
!CH2_RESET: IC13.12 (B4), X6.5
+3V3: C25.1, C27.2, C28.1, C30.1, C32.1, IC9.1 (VDD1), IC10.14 (VDD), IC11.8 (VDD2), IC12.8 (VDD2), IC13.1 (VDD1); also elsewhere on the board
CH1_5VDC: C26.1, C29.1, IC9.16 (VDD2), IC11.1 (VDD1), X5.2
CH1_GND: C26.2, C29.2, IC9.9 (GND2), IC11.4 (GND1), X5.10
CH1_MISO: IC11.2 (A1), X5.9
CH1_MOSI: IC9.15 (B1), X5.1
CH1_SCLK: IC9.10 (B6), X5.7
CH2_5VDC: C31.1, C33.1, IC12.1 (VDD1), IC13.16 (VDD2), X6.2
CH2_GND: C31.2, C33.2, IC12.4 (GND1), IC13.9 (GND2), X6.10
CH2_MISO: IC12.2 (A1), X6.9
CH2_MOSI: IC13.15 (B1), X6.1
CH2_SCLK: IC13.10 (B6), X6.7
GND: C25.2, C27.1, C28.2, C30.2, C32.2, IC9.8 (GND1), IC10.1 (OE), IC10.2 (I), IC10.4 (OE), IC10.5 (I), IC10.7 (VSS), IC11.5 (GND2), IC12.5 (GND2), IC13.8 (GND1); also elsewhere on the board
unnamed: IC10.12 (I), IC11.7 (B1)
unnamed: IC10.9 (I), IC12.7 (B1)

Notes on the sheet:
I/O isolators for communication with
post-regulator PCB
Not used
Ch #1 bus isolator
Ch #2 bus isolator

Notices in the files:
parts and their libraries:
EEZ_Lib1: This work is licensed under a Creative Commons Attribution-ShareAlike 4.0 International License.
